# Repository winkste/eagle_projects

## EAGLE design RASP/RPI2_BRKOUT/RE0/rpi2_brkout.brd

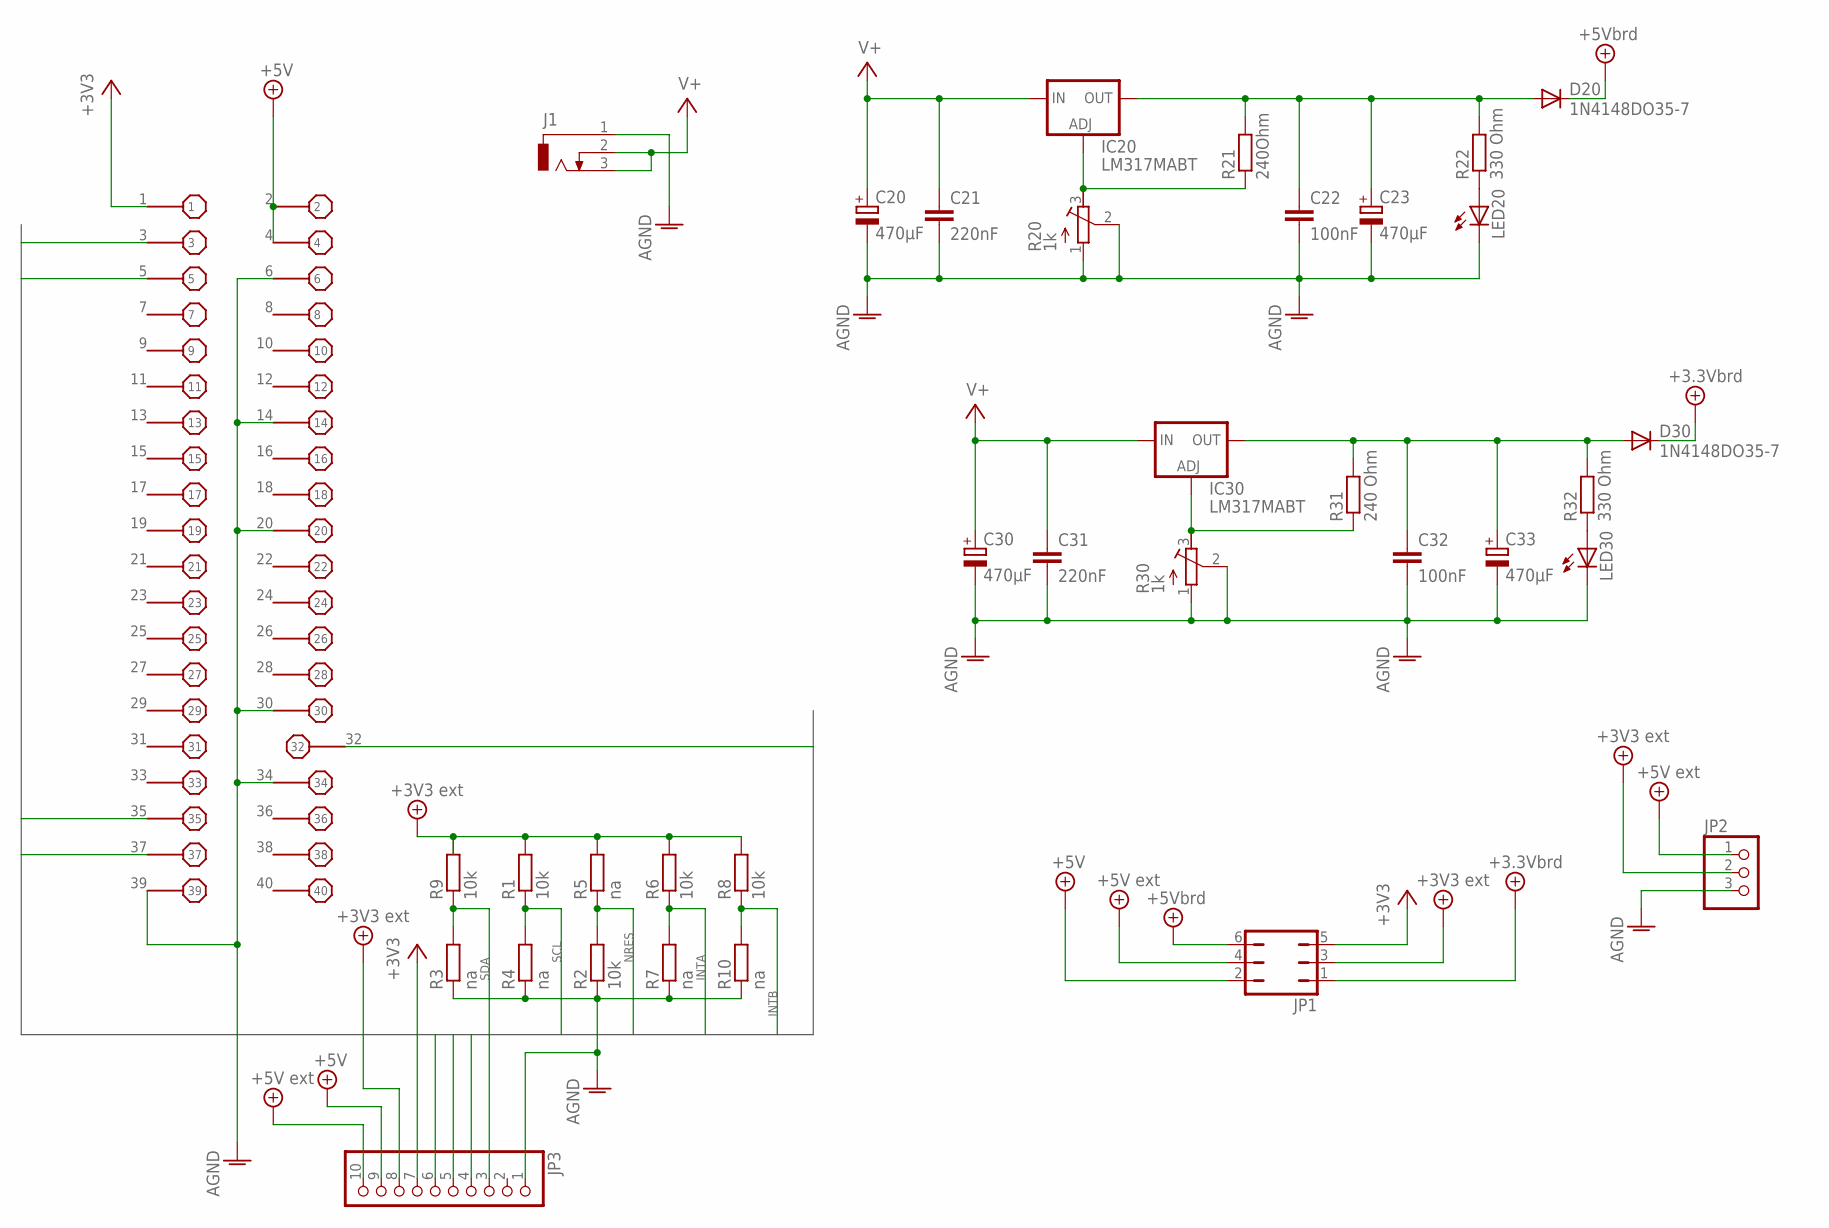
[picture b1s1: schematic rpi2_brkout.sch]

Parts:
C20, C23, C30, C33: 470µF; E5-10,5
C21, C31: 220nF; C050-030X075
C22, C32: 100nF; C025-025X050
D20, D30: 1N4148DO35-7; DO35-7
IC20, IC30: LM317MABT; TO220L1
J1: DCJ0303
JP1: JP3Q
JP2: PINHD-1X3; 1X03
JP3: PINHD-1X10; 1X10
LED20, LED30: LED5MM
R1, R2, R6, R8, R9: 10k; R0805
R3, R4, R5, R7, R10: na; R0805
R20, R30: 1k; RTRIM64W
R21: 240Ohm; 0207/10
R22, R32: 330 Ohm; 0207/10
R31: 240 Ohm; 0207/10
X1: B+_GPIO

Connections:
3.3VEXT: R1.2, R5.2, R6.2, R8.2, R9.2
+3V3: JP1.5, JP3.7, X1.1
+5V: JP1.2, JP3.9, X1.2, X1.4
+5V/1: JP1.4, JP2.1, JP3.10
+5V/2: JP1.3, JP2.2, JP3.8
+5V/3: D30.C, JP1.1
+5V/4: D20.C, JP1.6
AGND: C20.-, C21.2, C22.2, C23.-, C30.-, C31.2, C32.2, C33.-, J1.1, JP2.3, JP3.1, LED20.K (C), LED30.K (C), R2.1, R3.1, R4.1, R7.1, R10.1, R20.1 (A), R20.2 (S), R30.1 (A), R30.2 (S), X1.6, X1.14, X1.20, X1.30, X1.34, X1.39
INTA: JP3.5, R6.1, R7.2, X1.37
INTB: JP3.6, R8.1, R10.2, X1.35
unnamed: IC30.1 (ADJ), R30.3 (E), R31.1
unnamed: IC20.1 (ADJ), R20.3 (E), R21.1
unnamed: C22.1, C23.+, D20.A, IC20.2 (OUT), R21.2, R22.2
unnamed: LED20.A, R22.1
unnamed: C32.1, C33.+, D30.A, IC30.2 (OUT), R31.2, R32.2
unnamed: LED30.A, R32.1
NRES: R2.2, R5.1, X1.32
SCL: JP3.4, R1.1, R4.2, X1.5
SDA: JP3.3, R3.2, R9.1, X1.3
V+: C20.+, C21.1, C30.+, C31.1, IC20.3 (IN), IC30.3 (IN), J1.2, J1.3

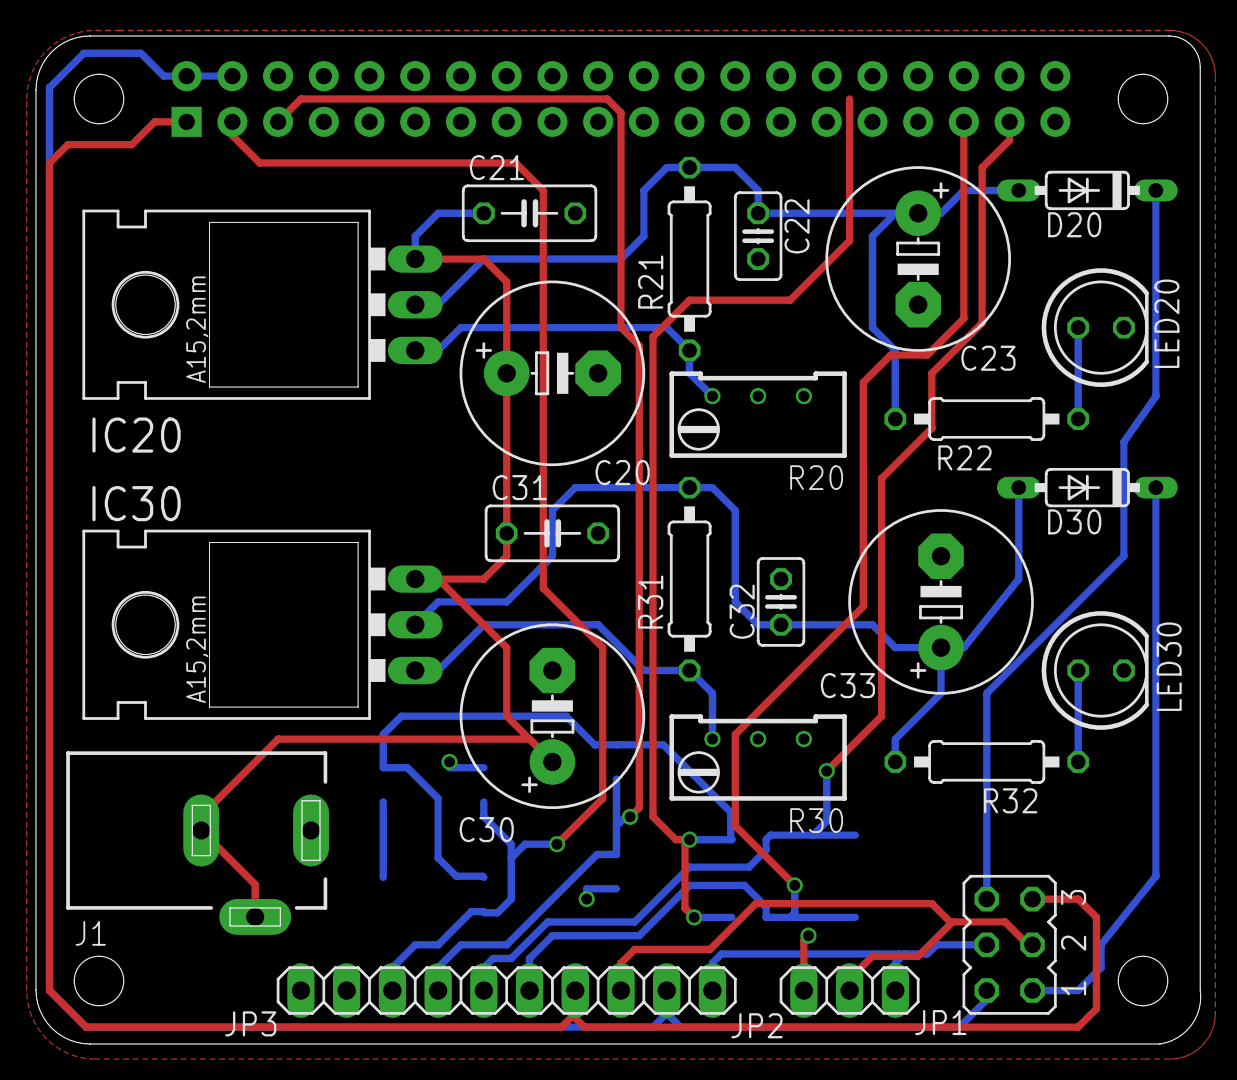
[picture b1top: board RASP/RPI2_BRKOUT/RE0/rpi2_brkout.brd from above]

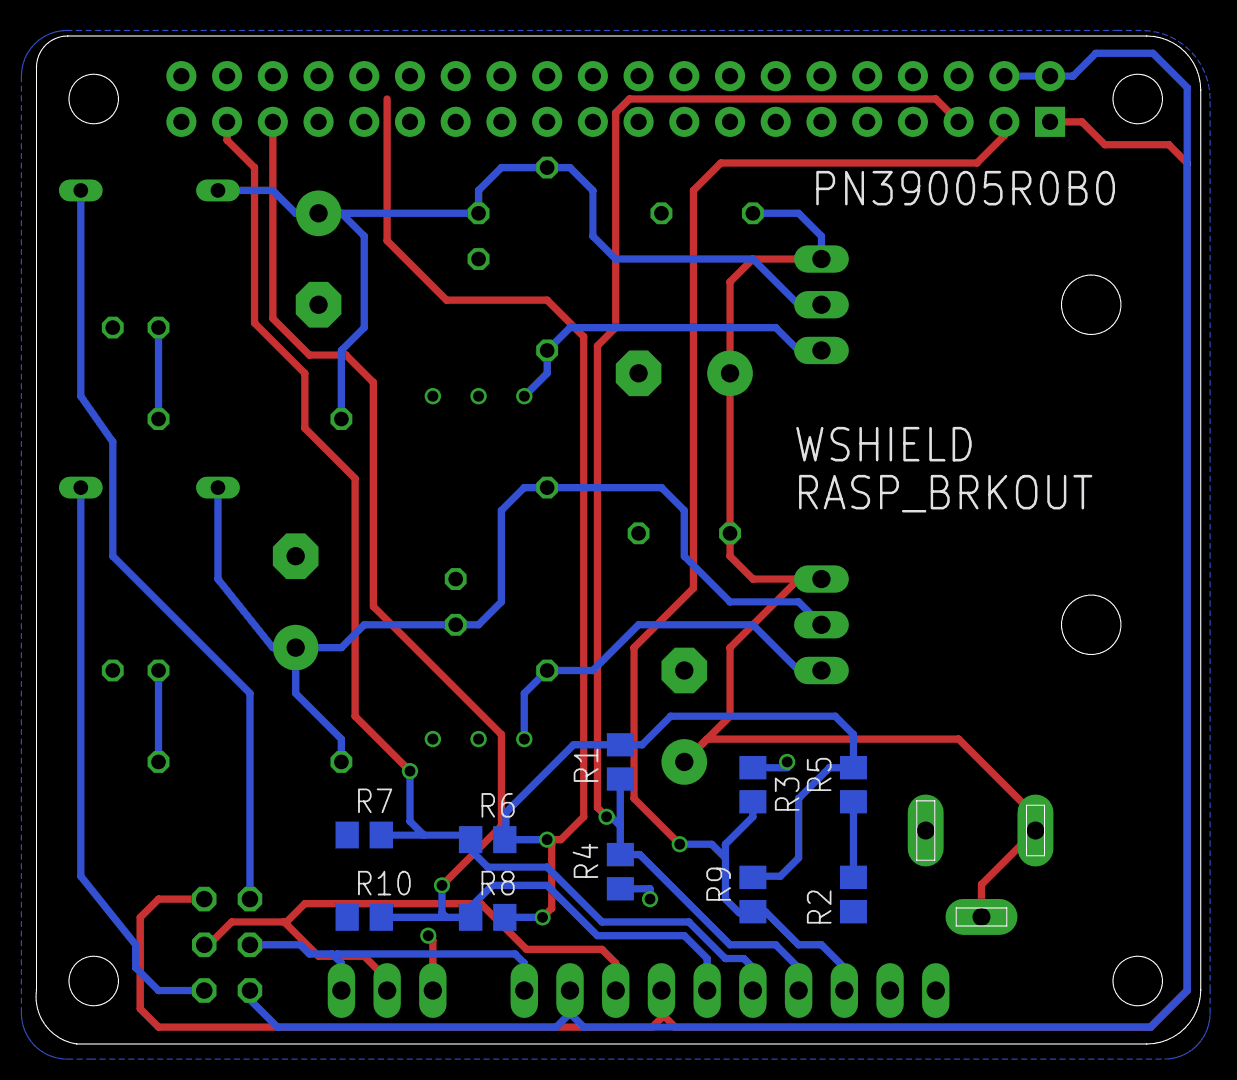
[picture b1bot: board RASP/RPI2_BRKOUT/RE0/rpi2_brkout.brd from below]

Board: 2 copper layers, 64.7 x 56.0 mm, 35 parts (10 on the bottom side), 20 nets.

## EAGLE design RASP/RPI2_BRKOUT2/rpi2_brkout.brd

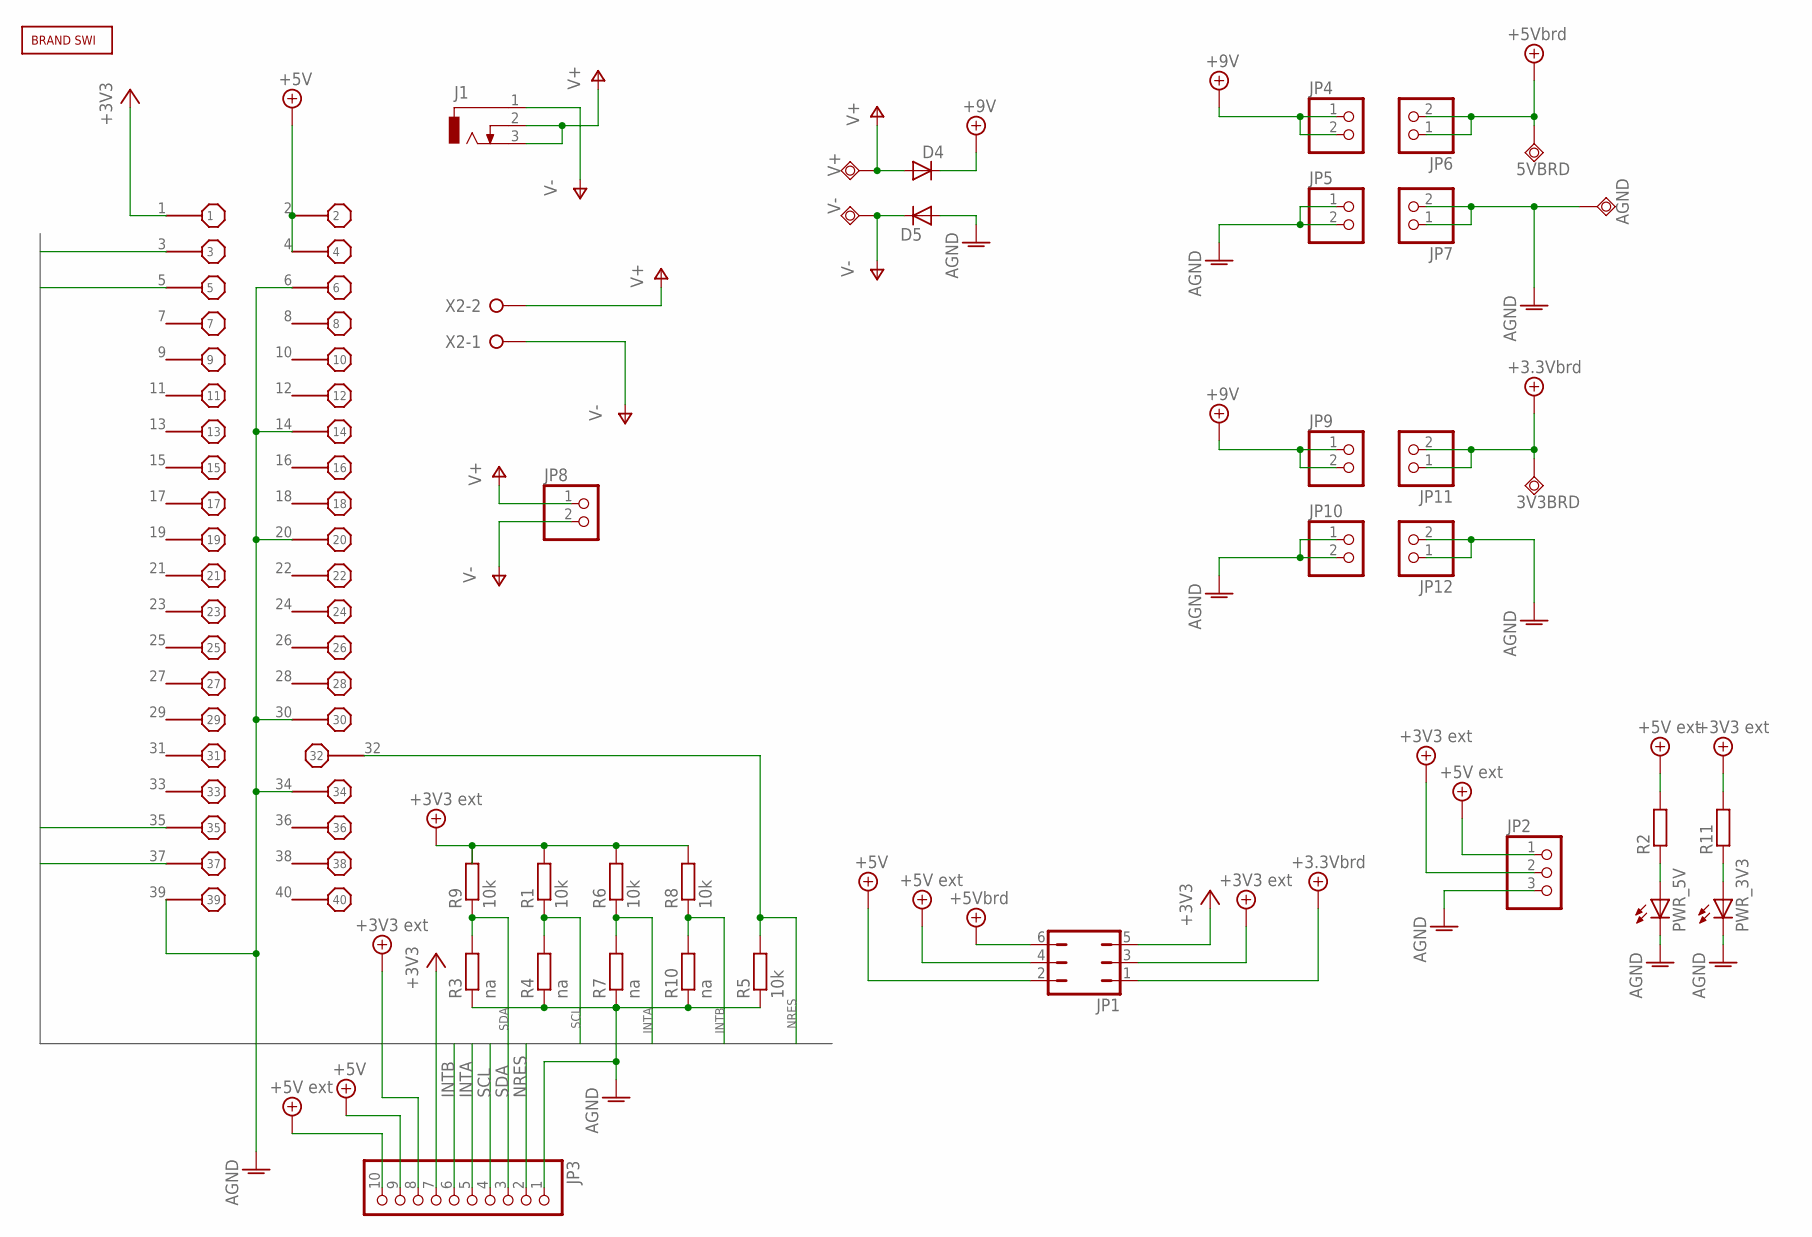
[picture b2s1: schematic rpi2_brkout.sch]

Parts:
3V3BRD, 5VBRD: TPSQTP20SQ; TP20SQ
AGND: TPSQTP20SQ; TP20SQ
D4, D5: 1N4148DO35-7; DO35-7
J1: DCJ0303
JP1: JP3Q
JP2: PINHD-1X3; 1X03
JP3: PINHD-1X10; 1X10
JP4, JP5, JP6, JP7, JP8, JP9, JP10, JP11, JP12: PINHD-1X2; 1X02
PWR_3V3, PWR_5V: LEDCHIP-LED0805; CHIP-LED0805
R1, R5, R6, R8, R9: 10k; R0805
R2, R11: R-EU_R0805; R0805
R3, R4, R7, R10: na; R0805
U$1: BRAND_SWI
V+: TPSQTP20SQ; TP20SQ
V-: TPSQTP20SQ; TP20SQ
X1: B+_GPIO
X2: W237-02P; W237-132

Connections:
3.3VEXT: R1.2, R6.2, R8.2, R9.2
+3V3: JP1.5, JP3.7, X1.1
+5V: JP1.2, JP3.9, X1.2, X1.4
+5V/1: JP1.4, JP2.1, JP3.10, R2.2
+5V/2: JP1.3, JP2.2, JP3.8, R11.2
+5V/3: 3V3BRD.TP, JP1.1, JP11.1, JP11.2
+5V/4: 5VBRD.TP, JP1.6, JP6.1, JP6.2
+9V: D4.C, JP4.1, JP4.2, JP9.1, JP9.2
AGND: AGND.TP, D5.A, JP2.3, JP3.1, JP5.1, JP5.2, JP7.1, JP7.2, JP10.1, JP10.2, JP12.1, JP12.2, PWR_3V3.C, PWR_5V.C, R3.1, R4.1, R5.1, R7.1, R10.1, X1.6, X1.14, X1.20, X1.30, X1.34, X1.39
INTA: JP3.5, R6.1, R7.2, X1.37
INTB: JP3.6, R8.1, R10.2, X1.35
unnamed: PWR_3V3.A, R11.1
unnamed: PWR_5V.A, R2.1
NRES: JP3.2, R5.2, X1.32
SCL: JP3.4, R1.1, R4.2, X1.5
SDA: JP3.3, R3.2, R9.1, X1.3
V+: D4.A, J1.2, J1.3, JP8.1, V+.TP, X2.2
V-: D5.C, J1.1, JP8.2, V-.TP, X2.1

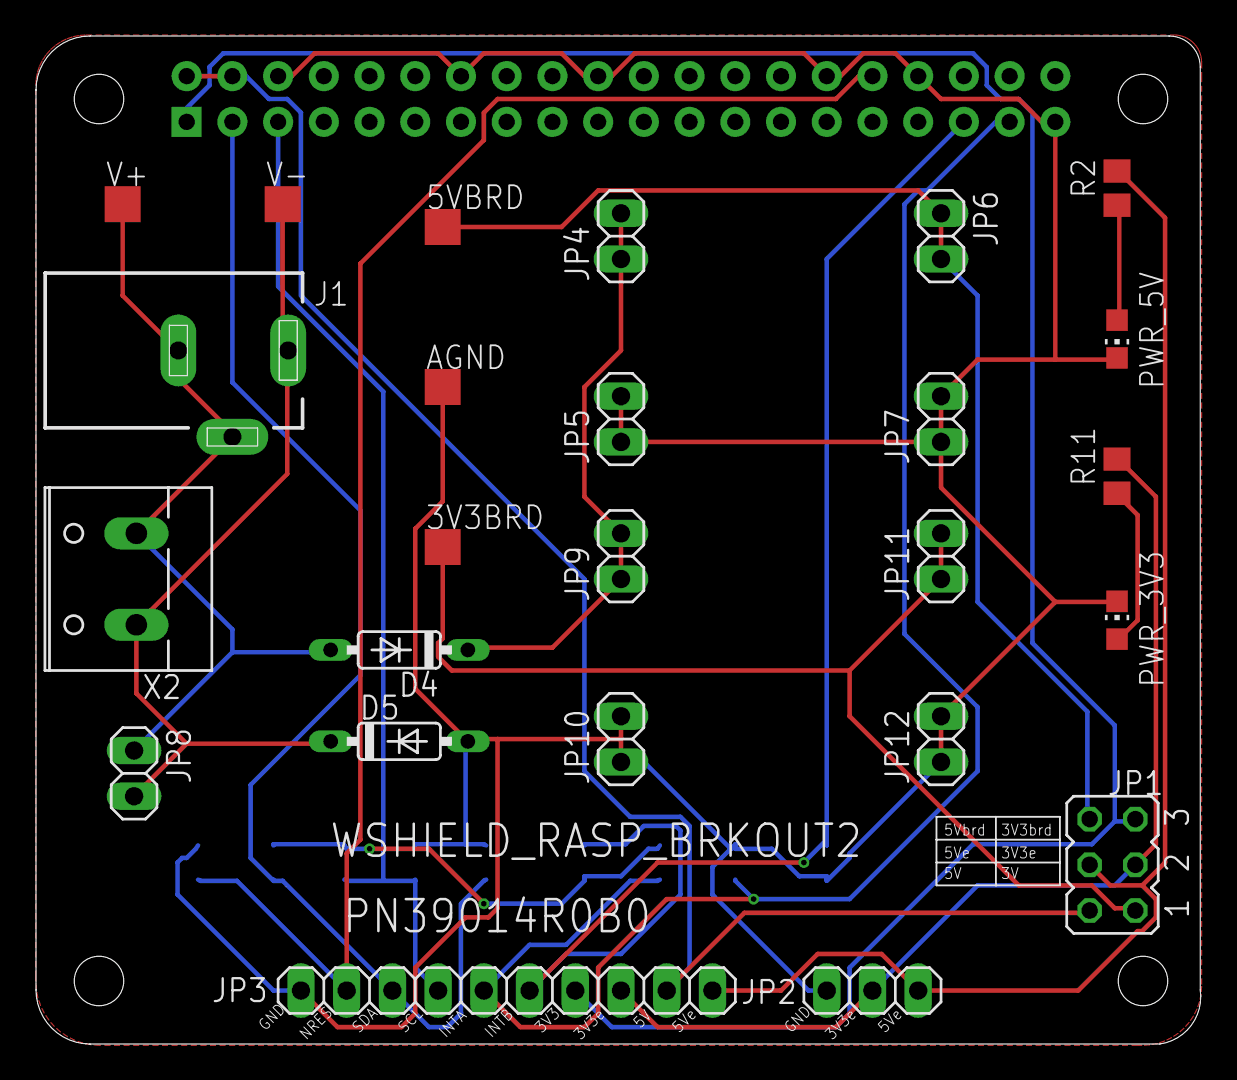
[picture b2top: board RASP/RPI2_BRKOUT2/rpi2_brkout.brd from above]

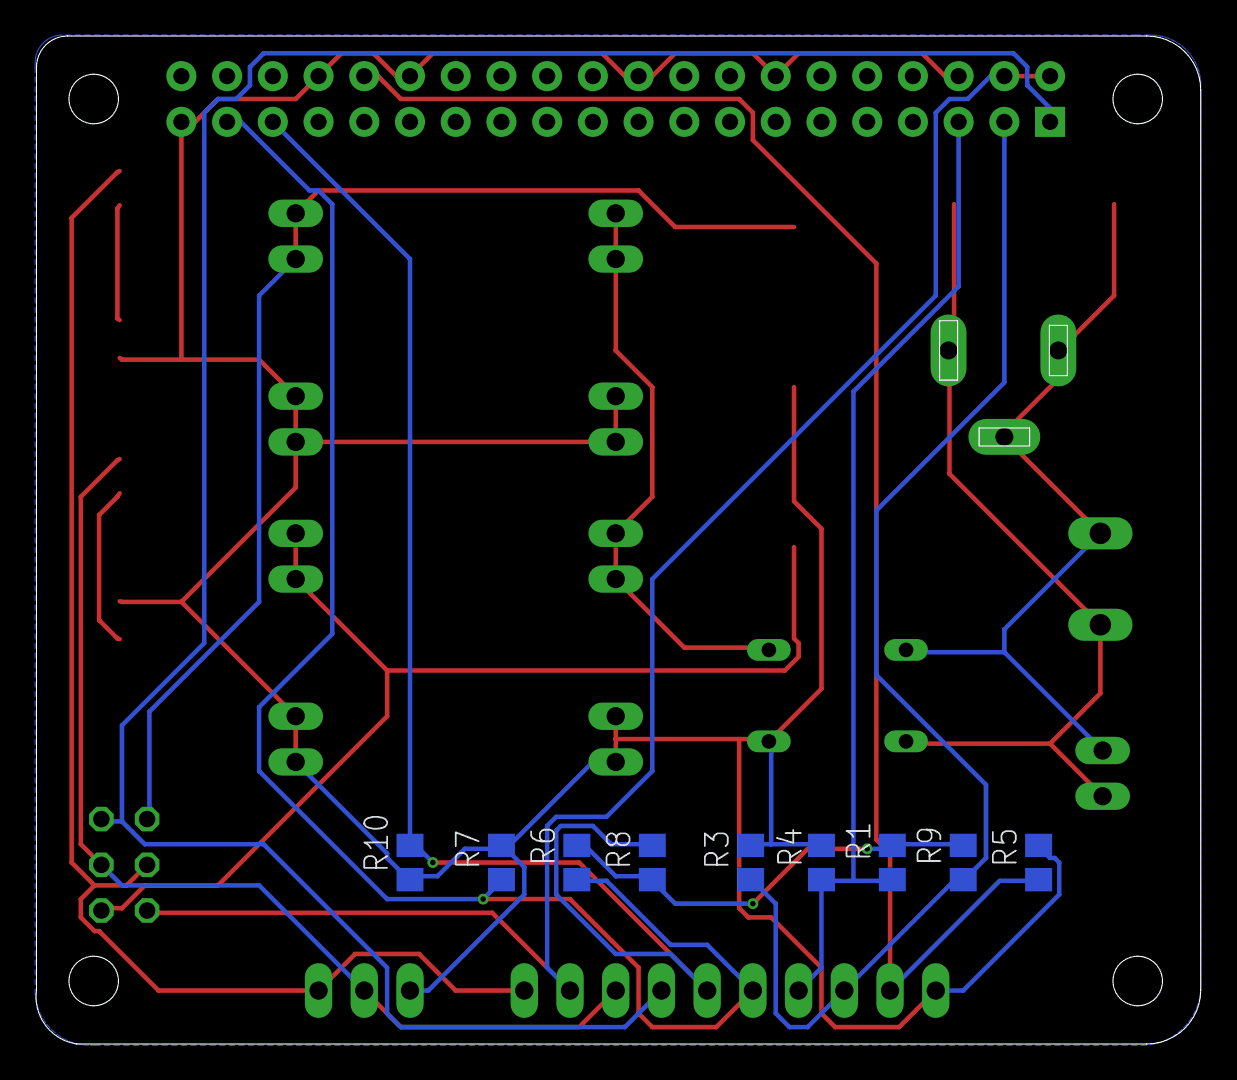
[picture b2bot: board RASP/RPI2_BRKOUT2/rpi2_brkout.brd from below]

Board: 2 copper layers, 64.7 x 56.0 mm, 36 parts (9 on the bottom side), 18 nets.

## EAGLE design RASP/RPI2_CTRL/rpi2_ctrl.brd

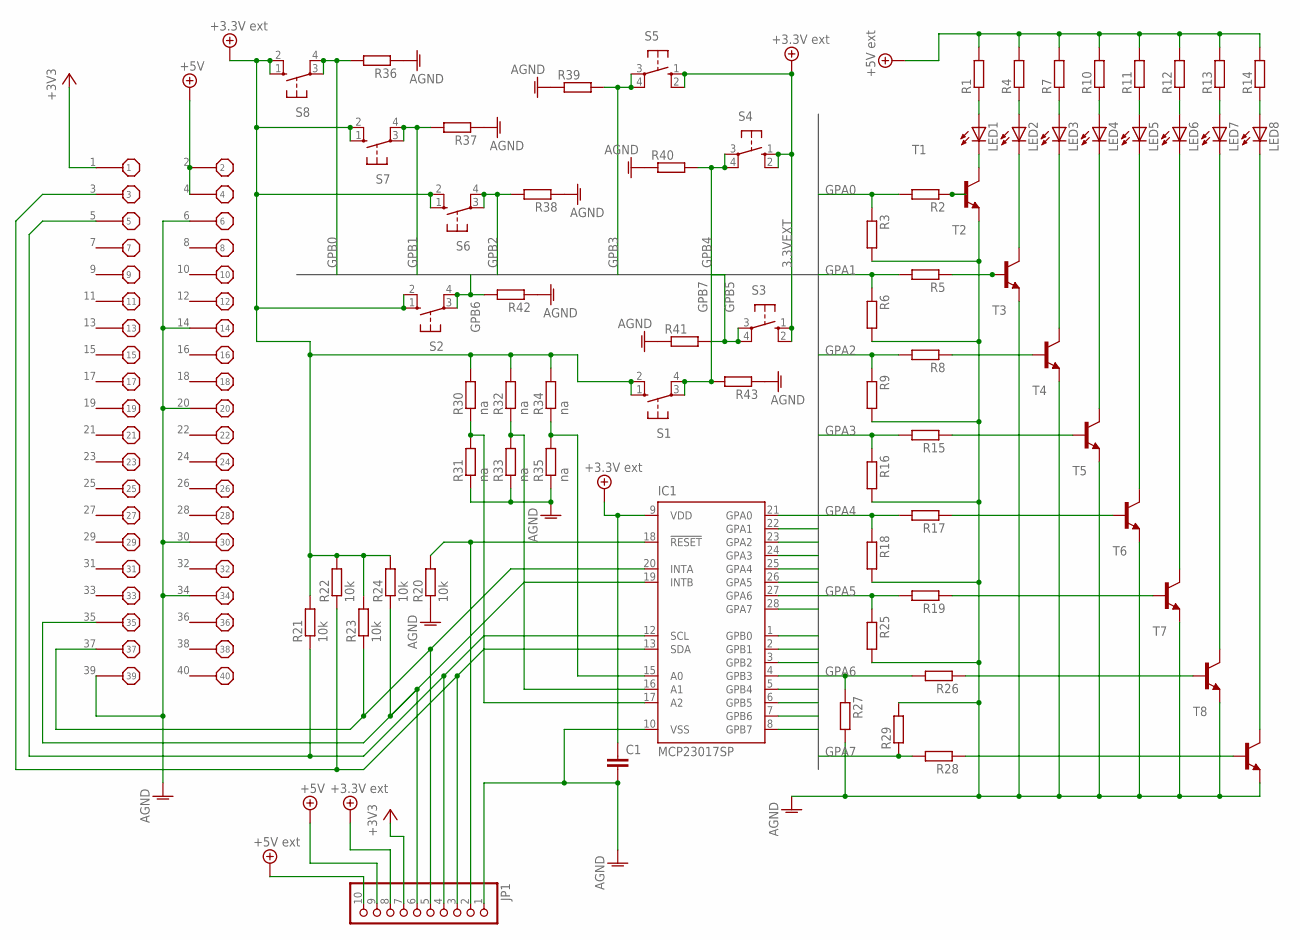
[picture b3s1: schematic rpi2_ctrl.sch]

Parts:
C1: C-EUC1210; C1210
IC1: MCP23017SP; DIL28-3
JP1: PINHD-1X10; 1X10
LED1, LED2, LED3, LED4, LED5, LED6, LED7, LED8: LED5MM
R1, R2, R3, R4, R5, R6, R7, R8, R9, R10, R11, R12, R13, R14, R15, R16, R17, R18, R19, R25, R26, R27, R28, R29, R36, R37, R38, R39, R40, R41, R42, R43: R-EU_R0805; R0805
R20, R21, R22, R23, R24: 10k; R0805
R30, R31, R32, R33, R34, R35: na; R0805
S1, S2, S3, S4, S5, S6, S7, S8: 10-XX; B3F-10XX
T1, T2, T3, T4, T5, T6, T7, T8: BC547-NPN-TO92-CBE; TO92-CBE
X1: B+_GPIO

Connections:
3.3VEXT: C1.1, IC1.9 (VDD), JP1.8, R21.2, R22.2, R23.2, R24.2, R30.2, R32.2, R34.2, S1.1 (S), S1.2 (S1), S2.1 (S), S2.2 (S1), S3.1 (S), S3.2 (S1), S4.1 (S), S4.2 (S1), S5.1 (S), S5.2 (S1), S6.1 (S), S6.2 (S1), S7.1 (S), S7.2 (S1), S8.1 (S), S8.2 (S1)
+3V3: JP1.7, X1.1
+5V: JP1.9, X1.2, X1.4
+5V/1: JP1.10, R1.2, R4.2, R7.2, R10.2, R11.2, R12.2, R13.2, R14.2
AGND: C1.2, IC1.10 (VSS), JP1.1, R3.2, R6.2, R9.2, R16.2, R18.2, R20.1, R25.2, R27.2, R29.2, R31.1, R33.1, R35.1, R36.1, R37.1, R38.1, R39.1, R40.1, R41.1, R42.1, R43.1, T1.E, T2.E, T3.E, T4.E, T5.E, T6.E, T7.E, T8.E, X1.6, X1.14, X1.20, X1.30, X1.34, X1.39
GPA0: IC1.21 (GPA0), R2.2, R3.1
GPA1: IC1.22 (GPA1), R5.2, R6.1
GPA2: IC1.23 (GPA2), R8.2, R9.1
GPA3: IC1.24 (GPA3), R15.2, R16.1
GPA4: IC1.25 (GPA4), R17.2, R18.1
GPA5: IC1.26 (GPA5), R19.2, R25.1
GPA6: IC1.27 (GPA6), R26.2, R27.1
GPA7: IC1.28 (GPA7), R28.2, R29.1
GPB0: IC1.1 (GPB0), R36.2, S8.3, S8.4 (P1)
GPB1: IC1.2 (GPB1), R37.2, S7.3, S7.4 (P1)
GPB2: IC1.3 (GPB2), R38.2, S6.3, S6.4 (P1)
GPB3: IC1.4 (GPB3), R39.2, S5.3, S5.4 (P1)
GPB4: IC1.5 (GPB4), R40.2, S4.3, S4.4 (P1)
GPB5: IC1.6 (GPB5), R41.2, S3.3, S3.4 (P1)
GPB6: IC1.7 (GPB6), R42.2, S2.3, S2.4 (P1)
GPB7: IC1.8 (GPB7), R43.2, S1.3, S1.4 (P1)
unnamed: R2.1, T1.B
unnamed: LED1.A, R1.1
unnamed: IC1.13 (SDA), JP1.3, R22.1, X1.3
unnamed: IC1.12 (SCL), JP1.4, R21.1, X1.5
unnamed: IC1.19 (INTB), JP1.6, R24.1, X1.35
unnamed: IC1.20 (INTA), JP1.5, R23.1, X1.37
unnamed: IC1.18 (!RESET), JP1.2, R20.2
unnamed: LED1.K (C), T1.C
unnamed: R5.1, T2.B
unnamed: LED2.A, R4.1
unnamed: LED2.K (C), T2.C
unnamed: R8.1, T3.B
unnamed: LED3.A, R7.1
unnamed: LED3.K (C), T3.C
unnamed: R15.1, T4.B
unnamed: LED4.K (C), T4.C
unnamed: R17.1, T5.B
unnamed: LED5.K (C), T5.C
unnamed: R19.1, T6.B
unnamed: LED6.K (C), T6.C
unnamed: R26.1, T7.B
unnamed: LED7.K (C), T7.C
unnamed: IC1.17 (A2), R30.1, R31.2
unnamed: R28.1, T8.B
unnamed: LED8.K (C), T8.C
unnamed: LED8.A, R14.1
unnamed: LED7.A, R13.1
unnamed: LED6.A, R12.1
unnamed: IC1.16 (A1), R32.1, R33.2
unnamed: IC1.15 (A0), R34.1, R35.2
unnamed: LED5.A, R11.1
unnamed: LED4.A, R10.1

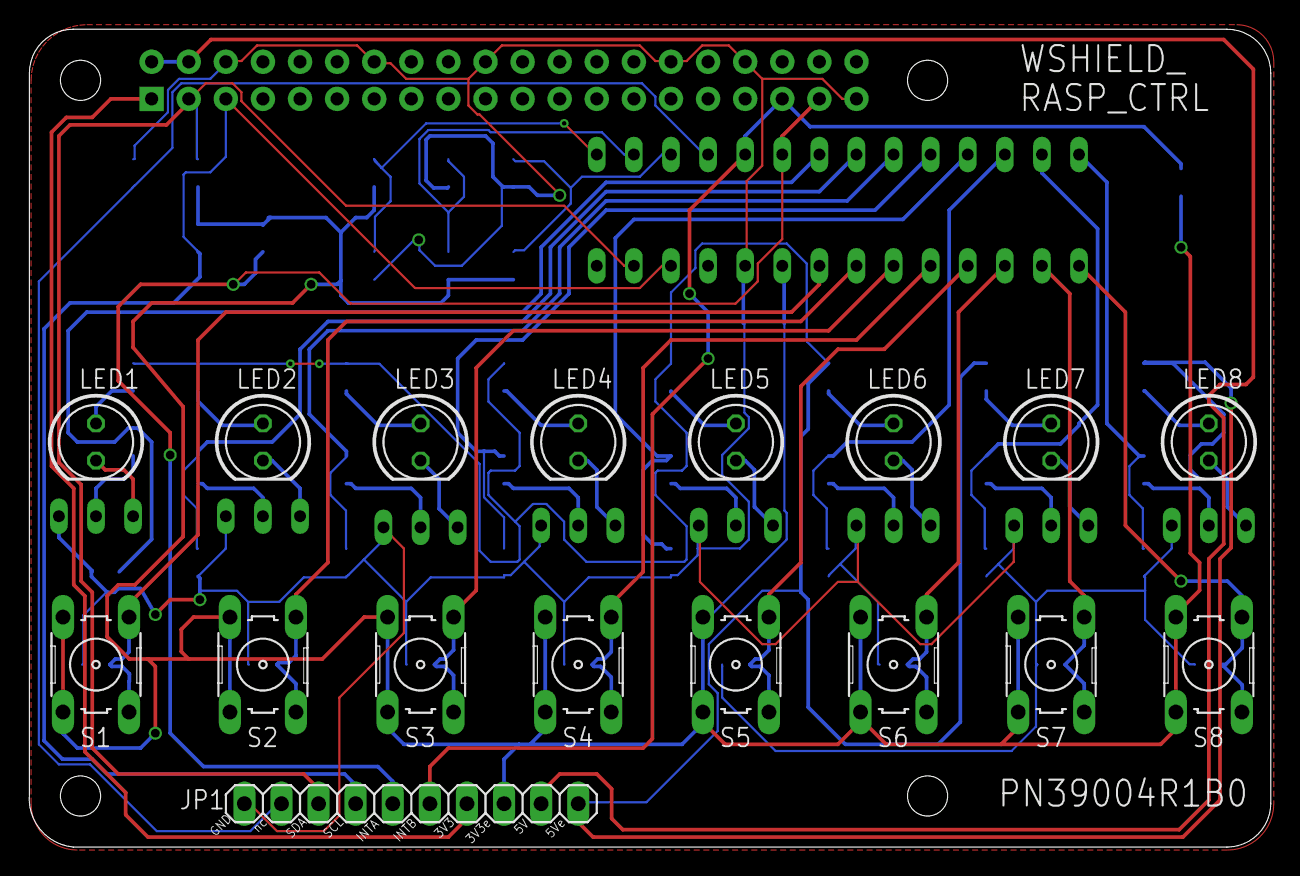
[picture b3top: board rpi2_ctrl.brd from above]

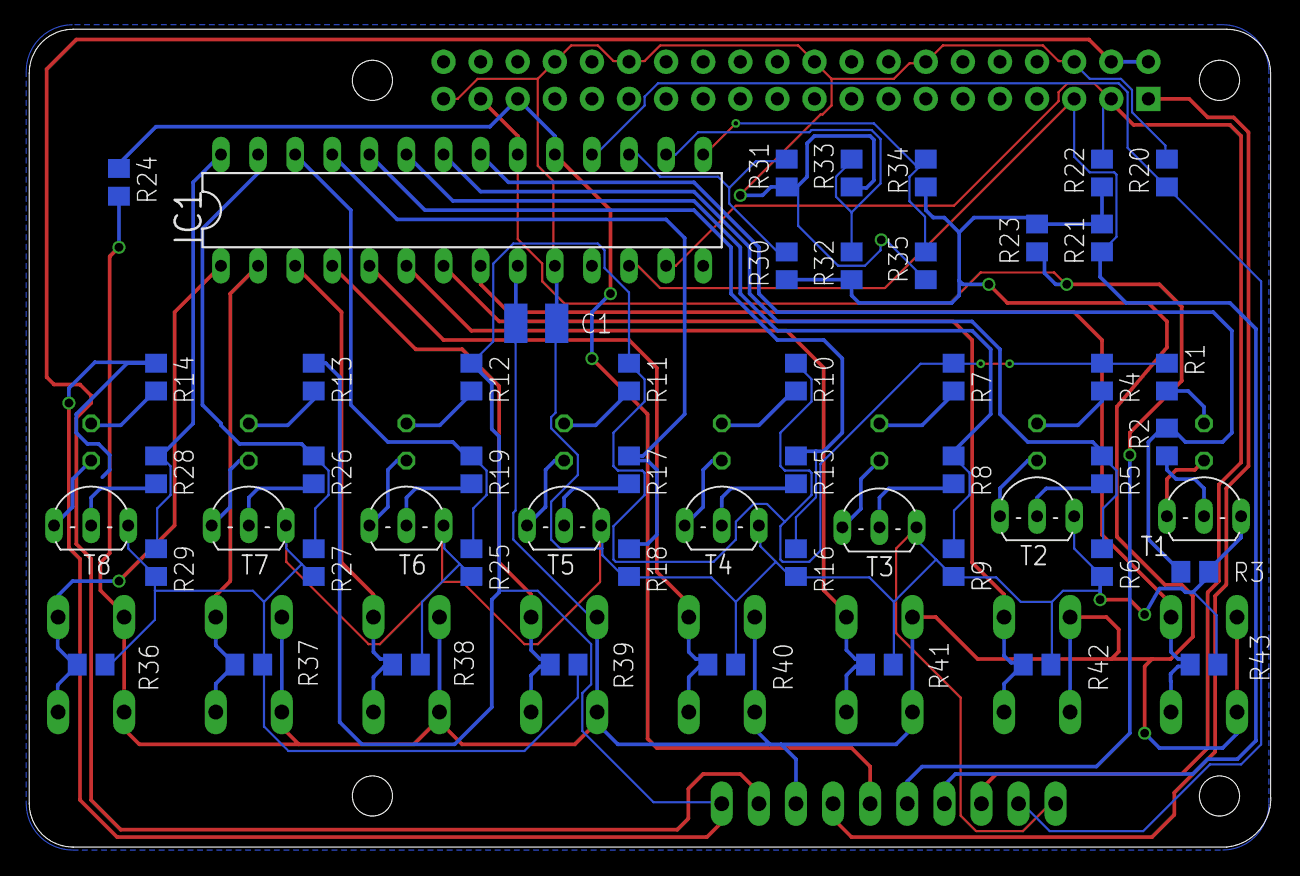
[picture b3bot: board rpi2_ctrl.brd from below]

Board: 2 copper layers, 85.0 x 56.0 mm, 71 parts (53 on the bottom side), 53 nets.

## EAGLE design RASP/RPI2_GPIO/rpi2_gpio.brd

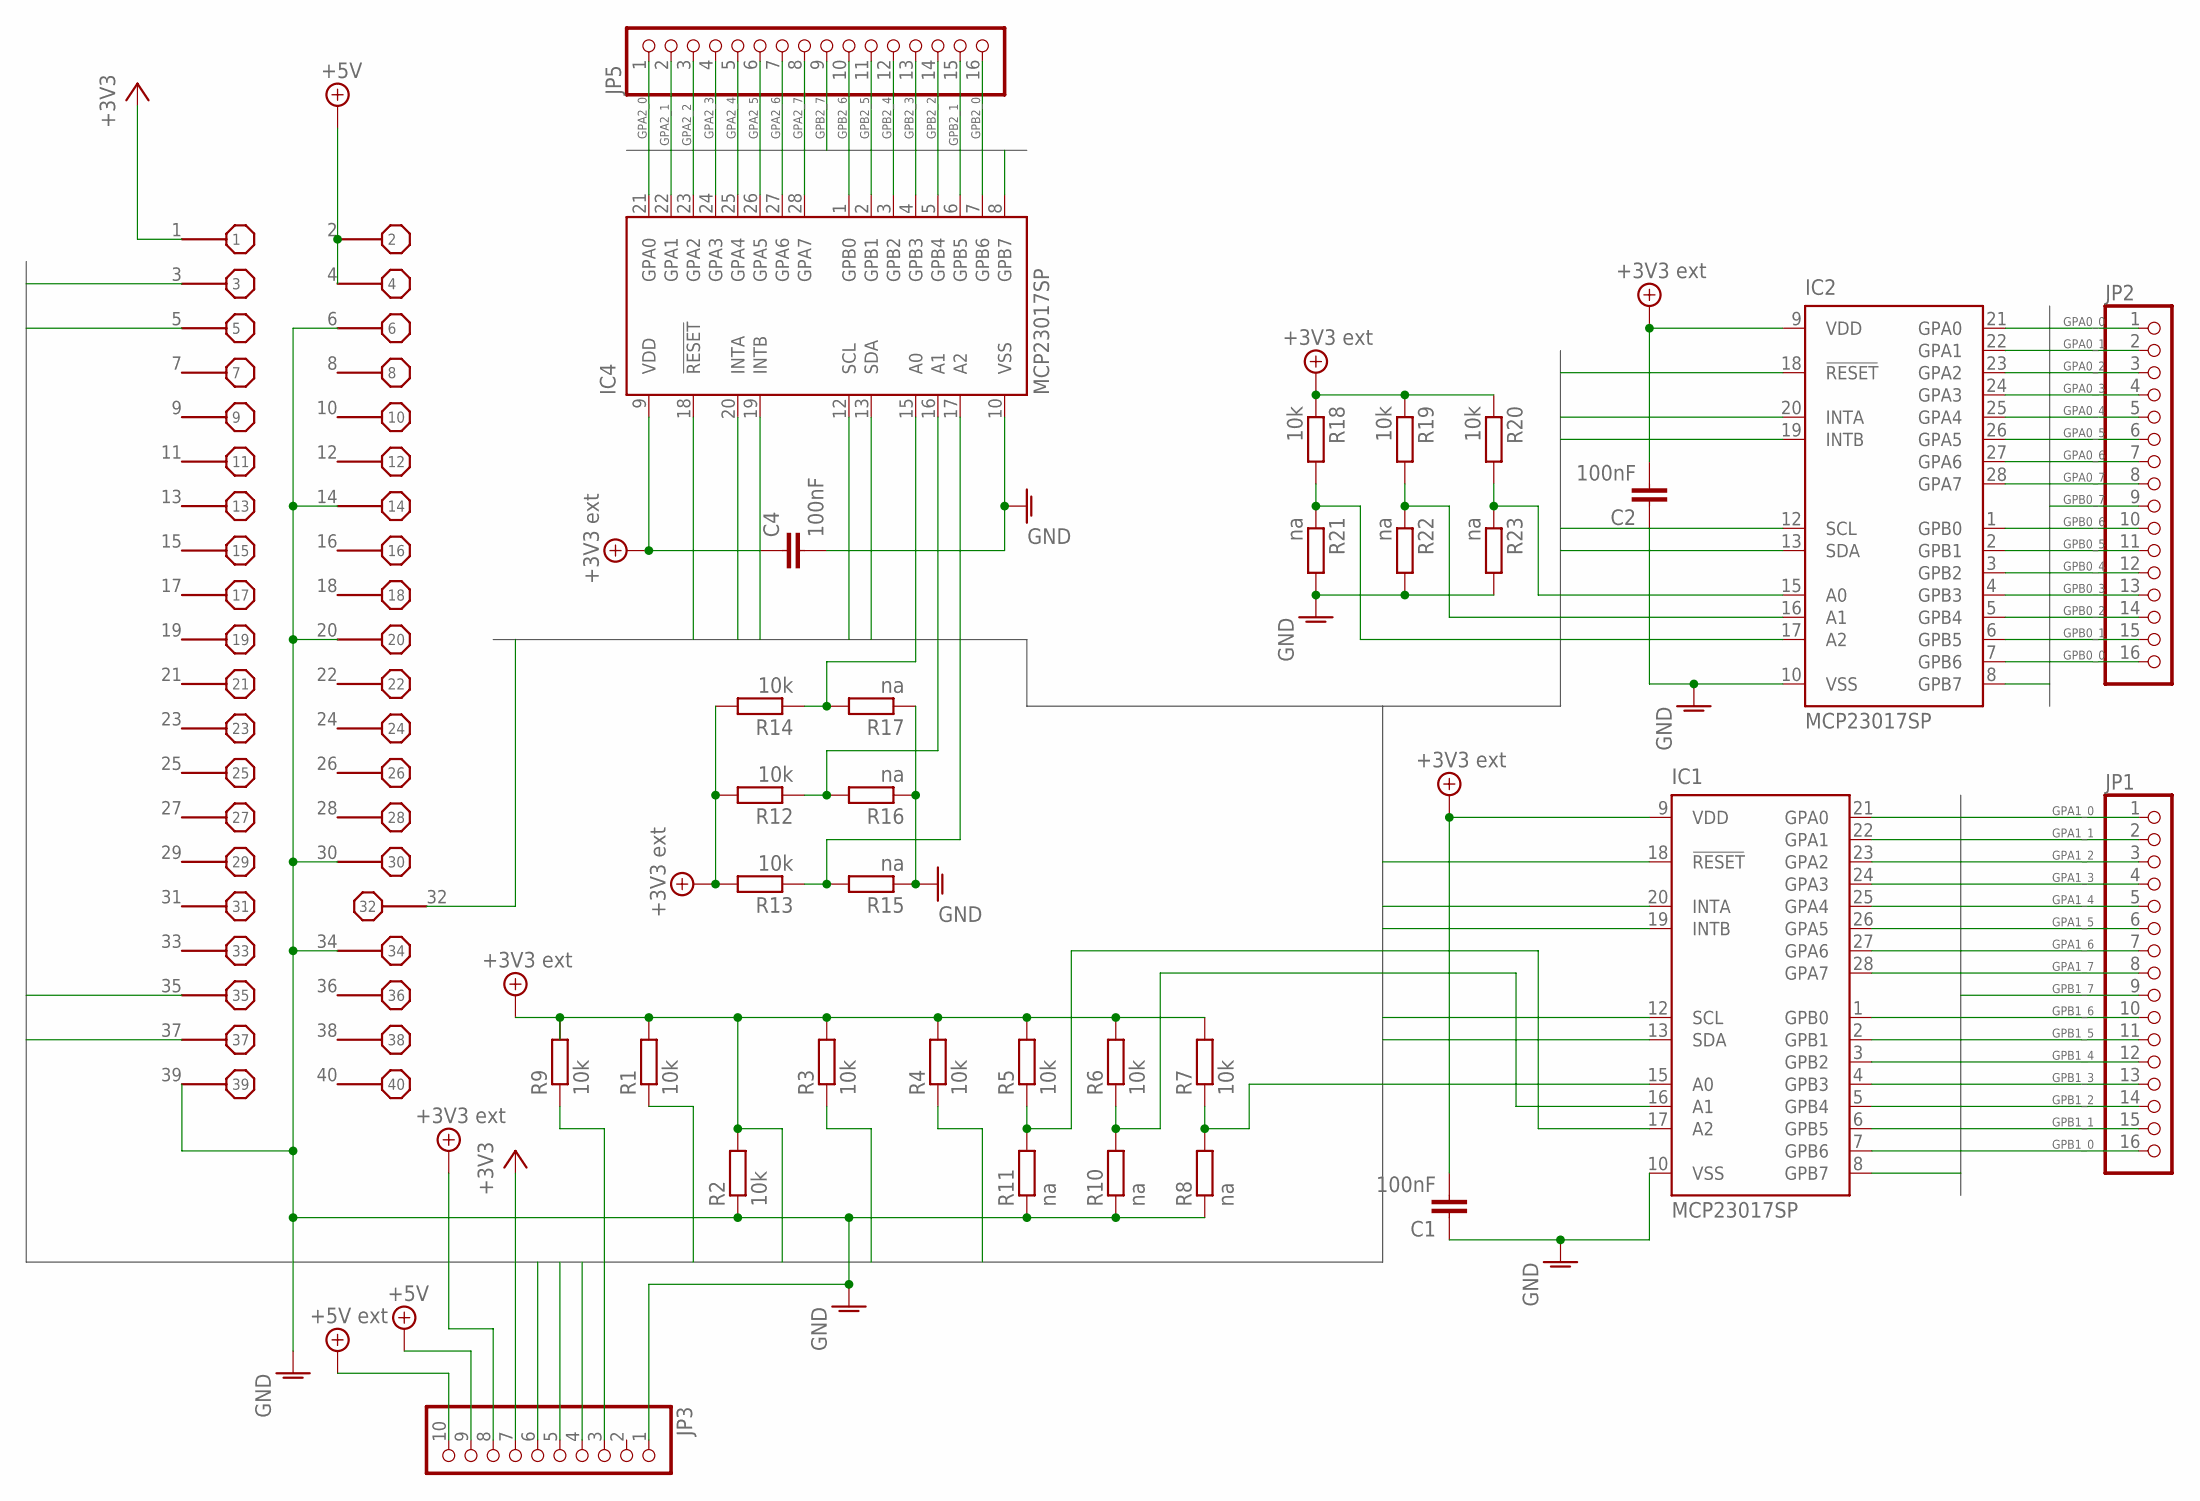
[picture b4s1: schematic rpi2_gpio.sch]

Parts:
C1, C2, C4: 100nF; C1210
IC1, IC2, IC4: MCP23017SP; DIL28-3
JP1, JP2, JP5: PINHD-1X16; 1X16
JP3: PINHD-1X10; 1X10
R1, R2, R3, R4, R5, R6, R7, R9, R12, R13, R14, R18, R19, R20: 10k; R0805
R8, R10, R11, R15, R16, R17, R21, R22, R23: na; R0805
X1: B+_GPIO

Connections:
3.3VEXT: IC1.18 (!RESET), IC2.18 (!RESET), IC4.18 (!RESET), R1.2, R2.2, R3.2, R4.2, R5.2, R6.2, R7.2, R9.2, X1.32
3V3EXT: C1.2, IC1.9 (VDD), R12.2, R13.2, R14.2, R18.1, R19.1, R20.1
+3V3: JP3.7, X1.1
+5V: JP3.9, X1.2, X1.4
+5V/1: JP3.10
+5V/2: C2.2, C4.1, IC2.9 (VDD), IC4.9 (VDD), JP3.8
GND: C1.1, C2.1, C4.2, IC1.10 (VSS), IC2.10 (VSS), IC4.10 (VSS), JP3.1, R2.1, R8.1, R10.1, R11.1, R15.1, R16.1, R17.1, R21.2, R22.2, R23.2, X1.6, X1.14, X1.20, X1.30, X1.34, X1.39
GPA0_0: IC2.21 (GPA0), JP2.1
GPA0_1: IC2.22 (GPA1), JP2.2
GPA0_2: IC2.23 (GPA2), JP2.3
GPA0_3: IC2.24 (GPA3), JP2.4
GPA0_4: IC2.25 (GPA4), JP2.5
GPA0_5: IC2.26 (GPA5), JP2.6
GPA0_6: IC2.27 (GPA6), JP2.7
GPA0_7: IC2.28 (GPA7), JP2.8
GPA1_0: IC1.21 (GPA0), JP1.1
GPA1_1: IC1.22 (GPA1), JP1.2
GPA1_2: IC1.23 (GPA2), JP1.3
GPA1_3: IC1.24 (GPA3), JP1.4
GPA1_4: IC1.25 (GPA4), JP1.5
GPA1_5: IC1.26 (GPA5), JP1.6
GPA1_6: IC1.27 (GPA6), JP1.7
GPA1_7: IC1.28 (GPA7), JP1.8
GPA2_0: IC4.21 (GPA0), JP5.1
GPA2_1: IC4.22 (GPA1), JP5.2
GPA2_2: IC4.23 (GPA2), JP5.3
GPA2_3: IC4.24 (GPA3), JP5.4
GPA2_4: IC4.25 (GPA4), JP5.5
GPA2_5: IC4.26 (GPA5), JP5.6
GPA2_6: IC4.27 (GPA6), JP5.7
GPA2_7: IC4.28 (GPA7), JP5.8
GPB0_0: IC2.1 (GPB0), JP2.16
GPB0_1: IC2.2 (GPB1), JP2.15
GPB0_2: IC2.3 (GPB2), JP2.14
GPB0_3: IC2.4 (GPB3), JP2.13
GPB0_4: IC2.5 (GPB4), JP2.12
GPB0_5: IC2.6 (GPB5), JP2.11
GPB0_6: IC2.7 (GPB6), JP2.10
GPB0_7: IC2.8 (GPB7), JP2.9
GPB1_0: IC1.1 (GPB0), JP1.16
GPB1_1: IC1.2 (GPB1), JP1.15
GPB1_2: IC1.3 (GPB2), JP1.14
GPB1_3: IC1.4 (GPB3), JP1.13
GPB1_4: IC1.5 (GPB4), JP1.12
GPB1_5: IC1.6 (GPB5), JP1.11
GPB1_6: IC1.7 (GPB6), JP1.10
GPB1_7: IC1.8 (GPB7), JP1.9
GPB2_0: IC4.1 (GPB0), JP5.16
GPB2_1: IC4.2 (GPB1), JP5.15
GPB2_2: IC4.3 (GPB2), JP5.14
GPB2_3: IC4.4 (GPB3), JP5.13
GPB2_4: IC4.5 (GPB4), JP5.12
GPB2_5: IC4.6 (GPB5), JP5.11
GPB2_6: IC4.7 (GPB6), JP5.10
GPB2_7: IC4.8 (GPB7), JP5.9
INTA: IC1.20 (INTA), IC2.20 (INTA), IC4.20 (INTA), JP3.5, R4.1, X1.37
INTB: IC1.19 (INTB), IC2.19 (INTB), IC4.19 (INTB), JP3.6, R3.1, X1.35
unnamed: IC1.17 (A2), R5.1, R11.2
unnamed: IC1.16 (A1), R6.1, R10.2
unnamed: IC2.17 (A2), R18.2, R21.1
unnamed: IC2.16 (A1), R19.2, R22.1
unnamed: IC1.15 (A0), R7.1, R8.2
unnamed: IC2.15 (A0), R20.2, R23.1
unnamed: IC4.17 (A2), R13.1, R15.2
unnamed: IC4.16 (A1), R12.1, R16.2
unnamed: IC4.15 (A0), R14.1, R17.2
SCL: IC1.12 (SCL), IC2.12 (SCL), IC4.12 (SCL), JP3.4, R1.1, X1.5
SDA: IC1.13 (SDA), IC2.13 (SDA), IC4.13 (SDA), JP3.3, R9.1, X1.3
